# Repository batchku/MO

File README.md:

# MO
Mobile Objects for Music (MOM), Mobile Object for Drawing (MOD), and ...

## Installation

First: clone this repo:
```
git clone git@github.com:batchku/MO.git
```

Then: This repo relies on a [aLib-pd](https://github.com/batchku/aLib-pd) as a submodule. You can either clone that repo separately, or use this command within the MO repository to pull the submodule:

```
git submodule update --init --recursive
```
### nameChange.sh

To test for resulting name change use "test":

```./nameChanger.sh test searchTerm wordToReplaceWith```

To actually change use "change":

```./nameChanger.sh change searchTerm wordToReplaceWith```

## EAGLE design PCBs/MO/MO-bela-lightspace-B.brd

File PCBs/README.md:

# PCBs
###   GERBERS
Gerber files for PCB orders
###   MO
Board + Schem files for MO, this is the primary PCB collection
###   MOM
Board + Schem files specifically for MOM
###   Processor
Header, .txt, and XML file generator code

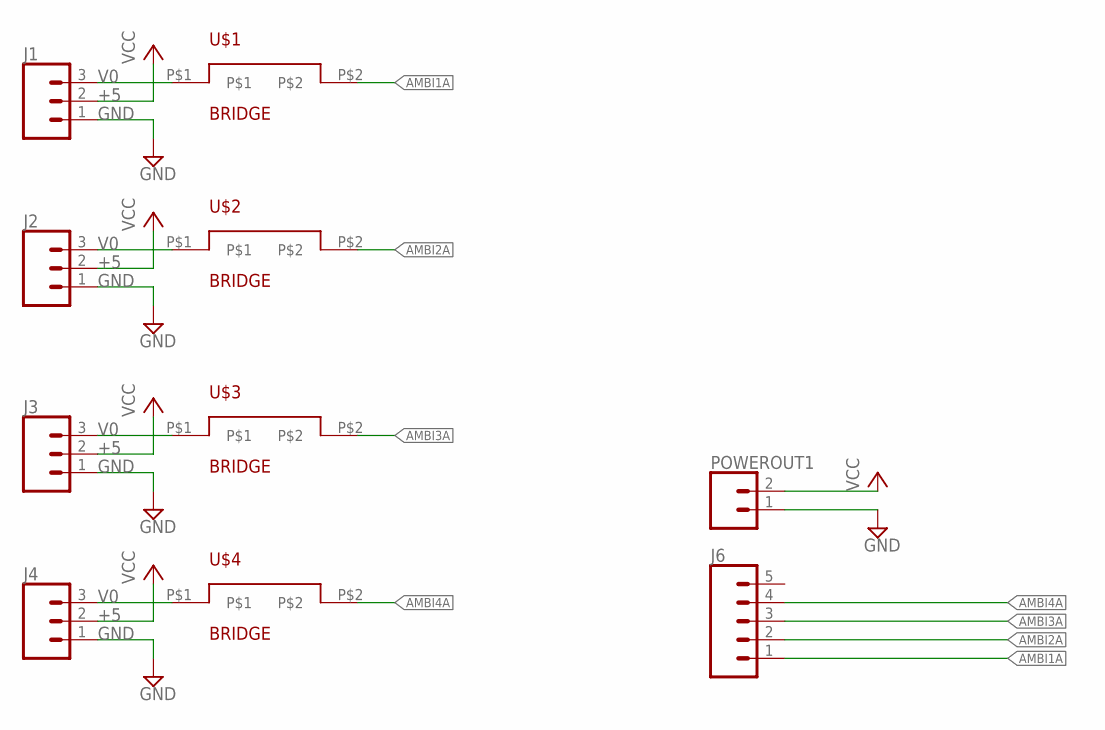
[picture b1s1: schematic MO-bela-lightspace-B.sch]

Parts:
J1, J2, J3, J4: CONN_03LOCK; 1X03_LOCK
J6: CONN_05LOCK; 1X05_LOCK
POWEROUT1: CONN_02LOCK; 1X02_LOCK
U$1, U$2, U$3, U$4: BRIDGE

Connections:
AMBI1A: J6.1, U$1.P$2
AMBI2A: J6.2, U$2.P$2
AMBI3A: J6.3, U$3.P$2
AMBI4A: J6.4, U$4.P$2
GND: J1.1, J2.1, J3.1, POWEROUT1.1
MNOVE: J4.1
unnamed: J1.3, U$1.P$1
unnamed: J2.3, U$2.P$1
unnamed: J3.3, U$3.P$1
unnamed: J4.3, U$4.P$1
VCC: J1.2, J2.2, J3.2, J4.2, POWEROUT1.2

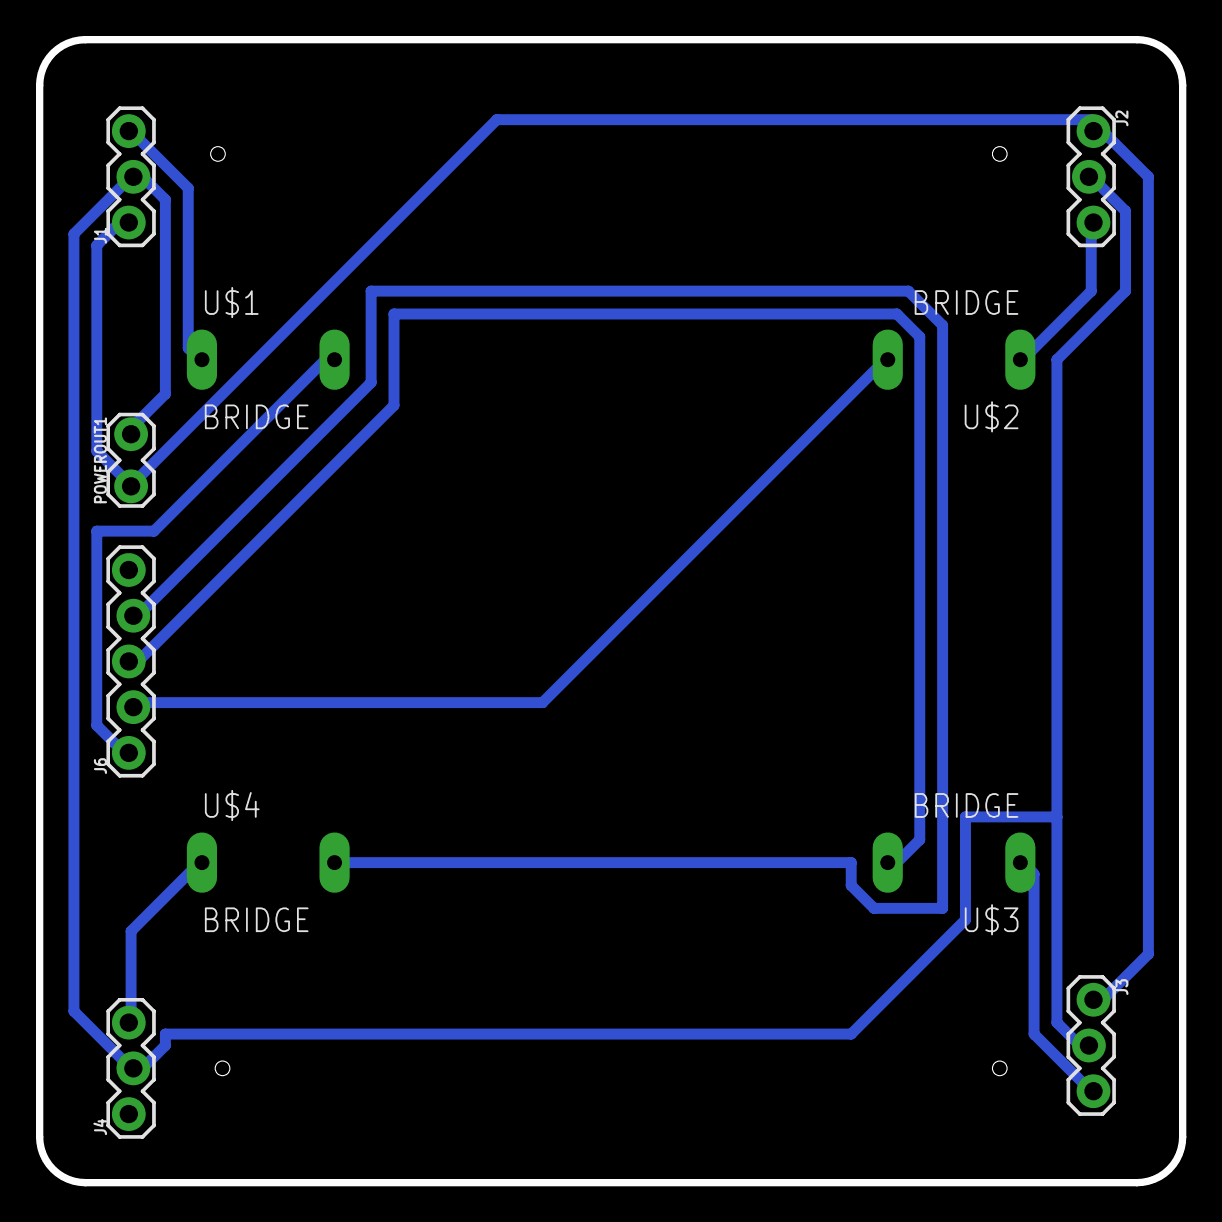
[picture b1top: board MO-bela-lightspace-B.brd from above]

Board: 2 copper layers, 63.5 x 63.5 mm, 10 parts (0 on the bottom side), 10 nets.

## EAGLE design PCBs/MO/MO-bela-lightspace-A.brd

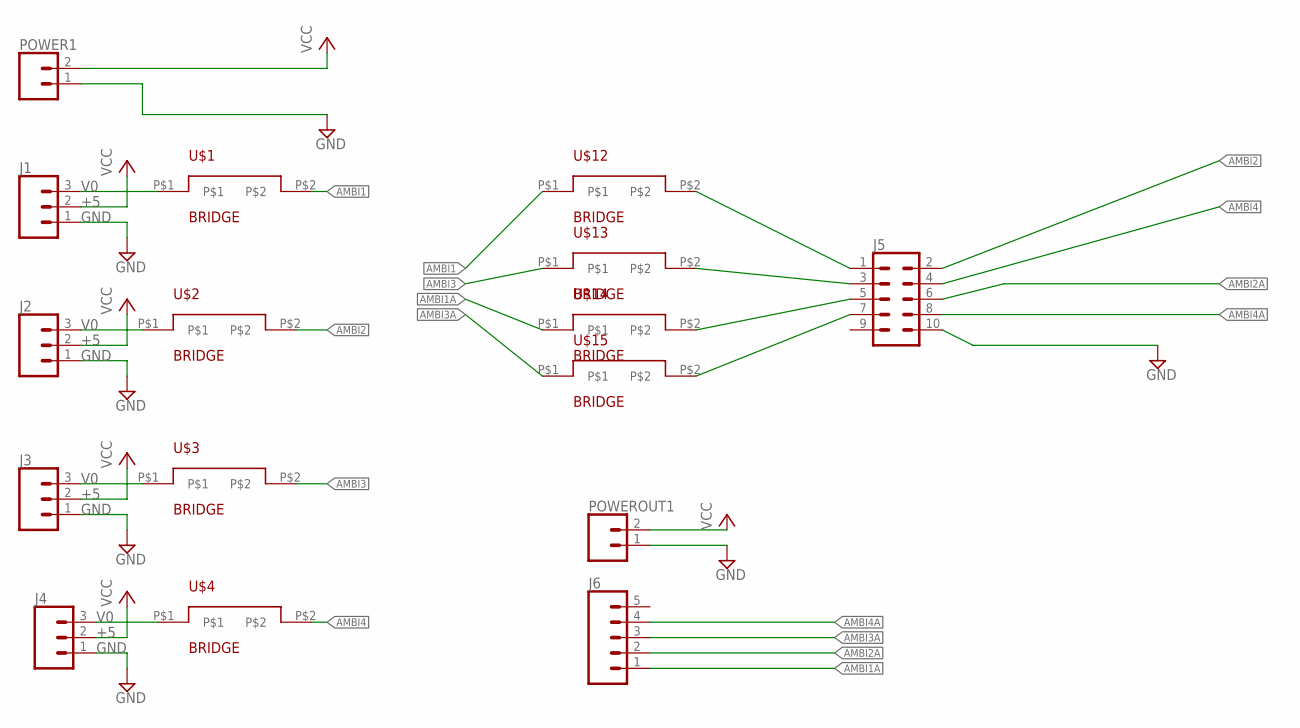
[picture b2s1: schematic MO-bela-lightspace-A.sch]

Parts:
J1, J2, J3, J4: CONN_03LOCK; 1X03_LOCK
J5: CONN_05X2SHD_LOCK; 2X5-SHROUDED_LOCK
J6: CONN_05LOCK; 1X05_LOCK
POWER1: CONN_02LOCK; 1X02_LOCK
POWEROUT1: CONN_02LOCK; 1X02_LOCK
U$1, U$2, U$3, U$4, U$12, U$13, U$14, U$15: BRIDGE

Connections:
AMBI1: U$1.P$2, U$12.P$1
AMBI1A: J6.1, U$14.P$1
AMBI2: J5.2, U$2.P$2
AMBI2A: J5.6, J6.2
AMBI3: U$3.P$2, U$13.P$1
AMBI3A: J6.3, U$15.P$1
AMBI4: J5.4, U$4.P$2
AMBI4A: J5.8, J6.4
GND: J1.1, J2.1, J3.1, J4.1, J5.10, POWER1.1, POWEROUT1.1
unnamed: J1.3, U$1.P$1
unnamed: J2.3, U$2.P$1
unnamed: J3.3, U$3.P$1
unnamed: J4.3, U$4.P$1
unnamed: J5.1, U$12.P$2
unnamed: J5.3, U$13.P$2
unnamed: J5.5, U$14.P$2
unnamed: J5.7, U$15.P$2
VCC: J1.2, J2.2, J3.2, J4.2, POWER1.2, POWEROUT1.2

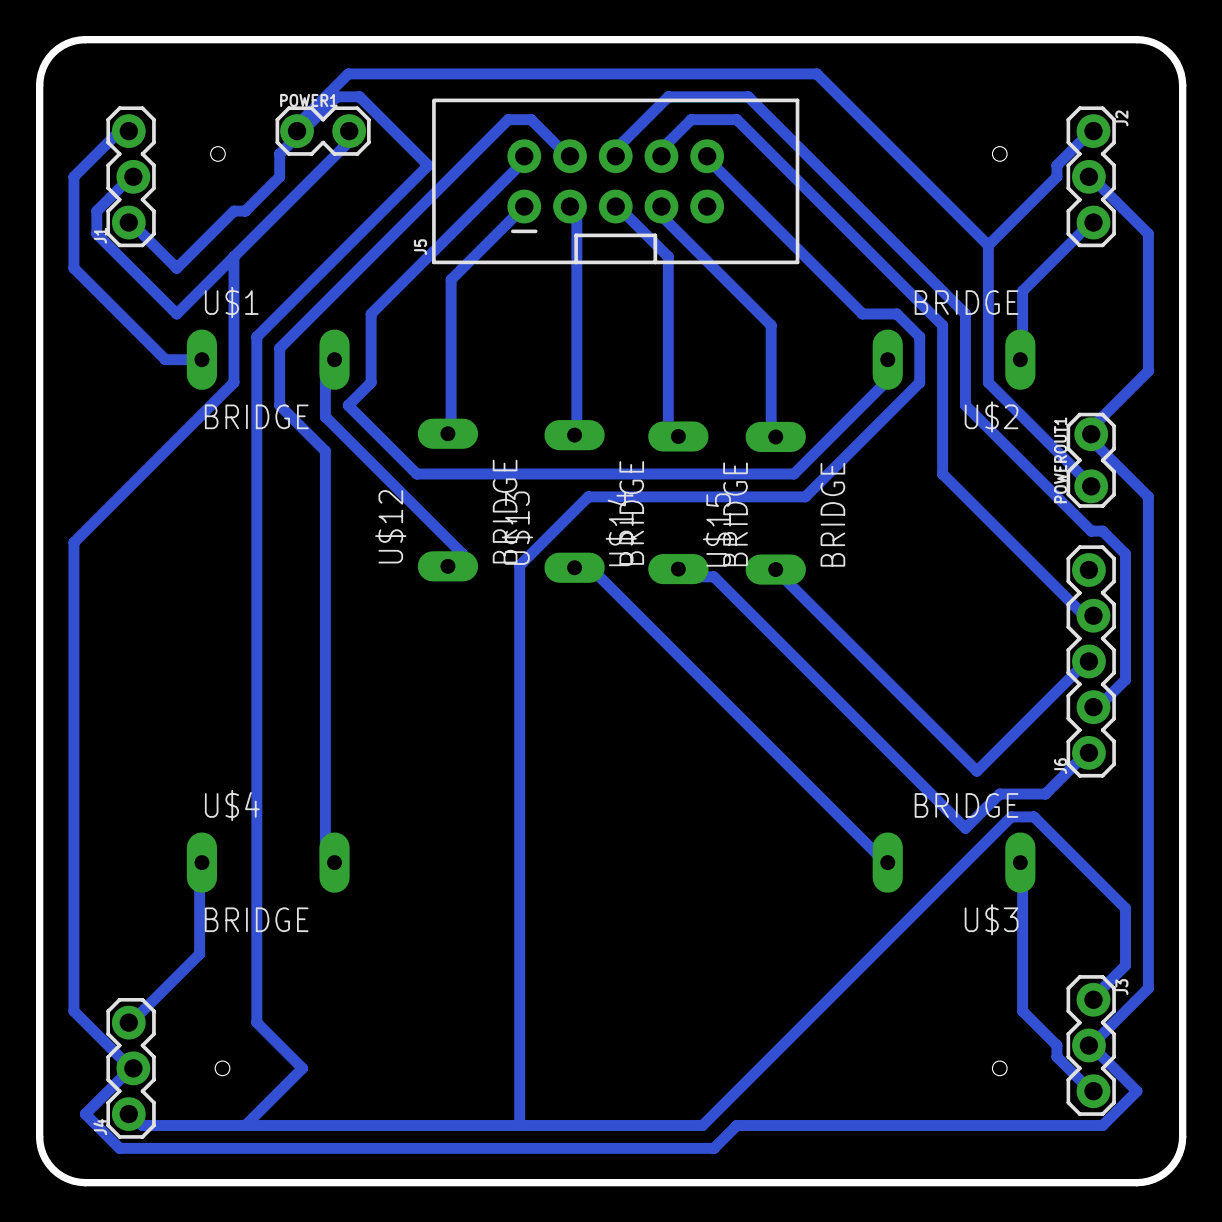
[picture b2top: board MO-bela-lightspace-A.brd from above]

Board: 2 copper layers, 63.5 x 63.5 mm, 16 parts (0 on the bottom side), 18 nets.

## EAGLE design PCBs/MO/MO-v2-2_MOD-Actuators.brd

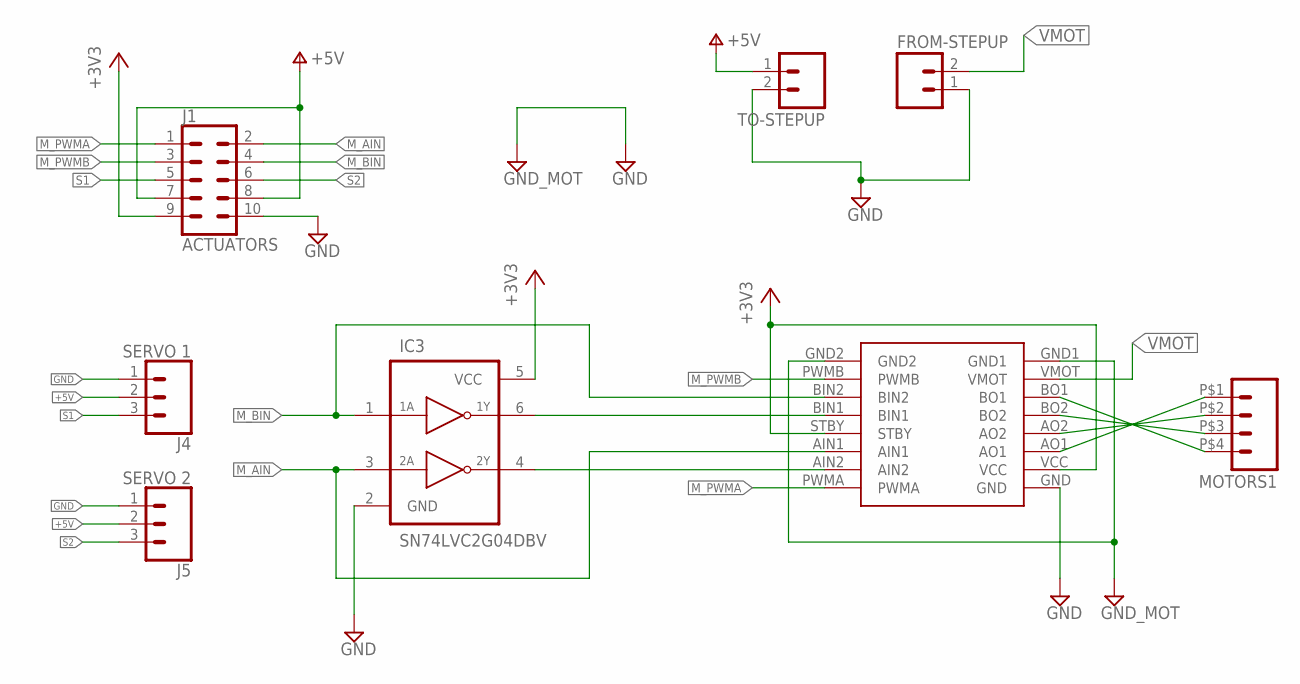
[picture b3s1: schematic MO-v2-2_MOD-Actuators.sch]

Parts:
FROM-STEPUP: M02LOCK; 1X02_LOCK
IC3: SN74LVC2G04DBV; SOT23-6
J1: ACTUATORS; 2X5-SHROUDED_LOCK
J4: SERVO 1; 1X03_LOCK@1
J5: SERVO 2; 1X03_LOCK@1
MOTORS1: M04; SPRINGTERMINAL-2.54MM-4
TO-STEPUP: M02LOCK; 1X02_LOCK
U$7: POLOLU_TB6612FNG

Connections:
+3V3: IC3.5 (VCC), J1.9, U$7.STBY, U$7.VCC
+5V: J1.7, J1.8, J4.2, J5.2, TO-STEPUP.1
GND: FROM-STEPUP.1, IC3.2 (GND), J1.10, J4.1, J5.1, TO-STEPUP.2, U$7.GND
GND_MOT: U$7.GND1, U$7.GND2
M_AIN: IC3.3 (2A), J1.2, U$7.AIN1
M_BIN: IC3.1 (1A), J1.4, U$7.BIN2
M_PWMA: J1.1, U$7.PWMA
M_PWMB: J1.3, U$7.PWMB
unnamed: MOTORS1.P$1 (1), U$7.AO1
unnamed: MOTORS1.P$2 (2), U$7.AO2
unnamed: MOTORS1.P$3 (3), U$7.BO2
unnamed: MOTORS1.P$4 (4), U$7.BO1
unnamed: IC3.6 (1Y), U$7.BIN1
unnamed: IC3.4 (2Y), U$7.AIN2
S1: J1.5, J4.3
S2: J1.6, J5.3
VMOT: FROM-STEPUP.2, U$7.VMOT

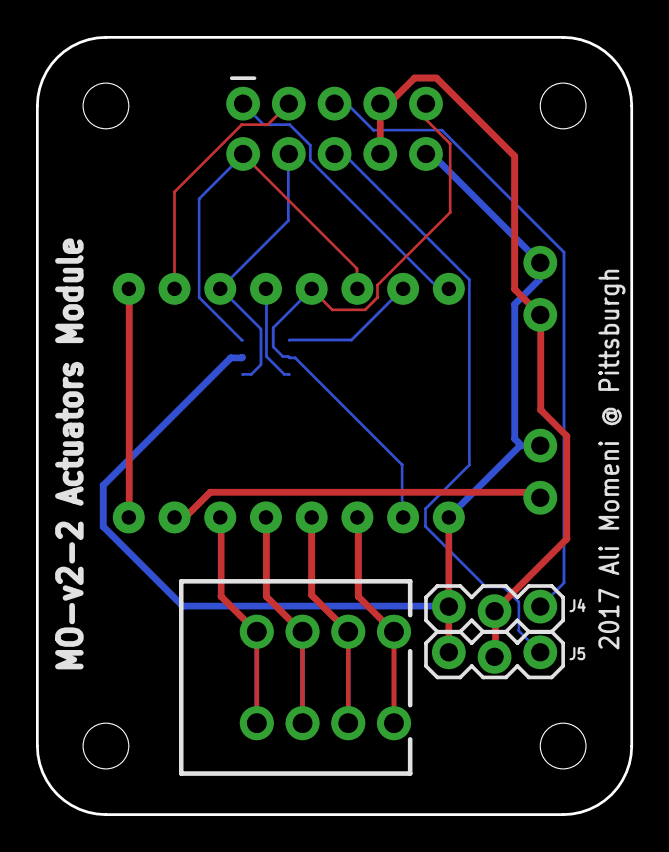
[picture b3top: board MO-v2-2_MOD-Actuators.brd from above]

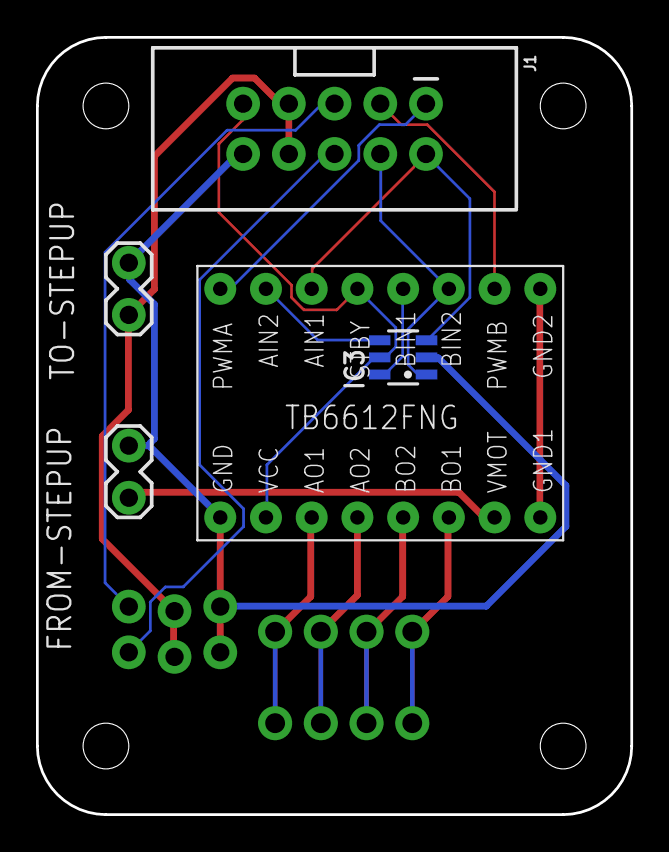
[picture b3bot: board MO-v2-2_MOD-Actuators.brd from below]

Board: 2 copper layers, 33.0 x 43.2 mm, 8 parts (5 on the bottom side), 17 nets.

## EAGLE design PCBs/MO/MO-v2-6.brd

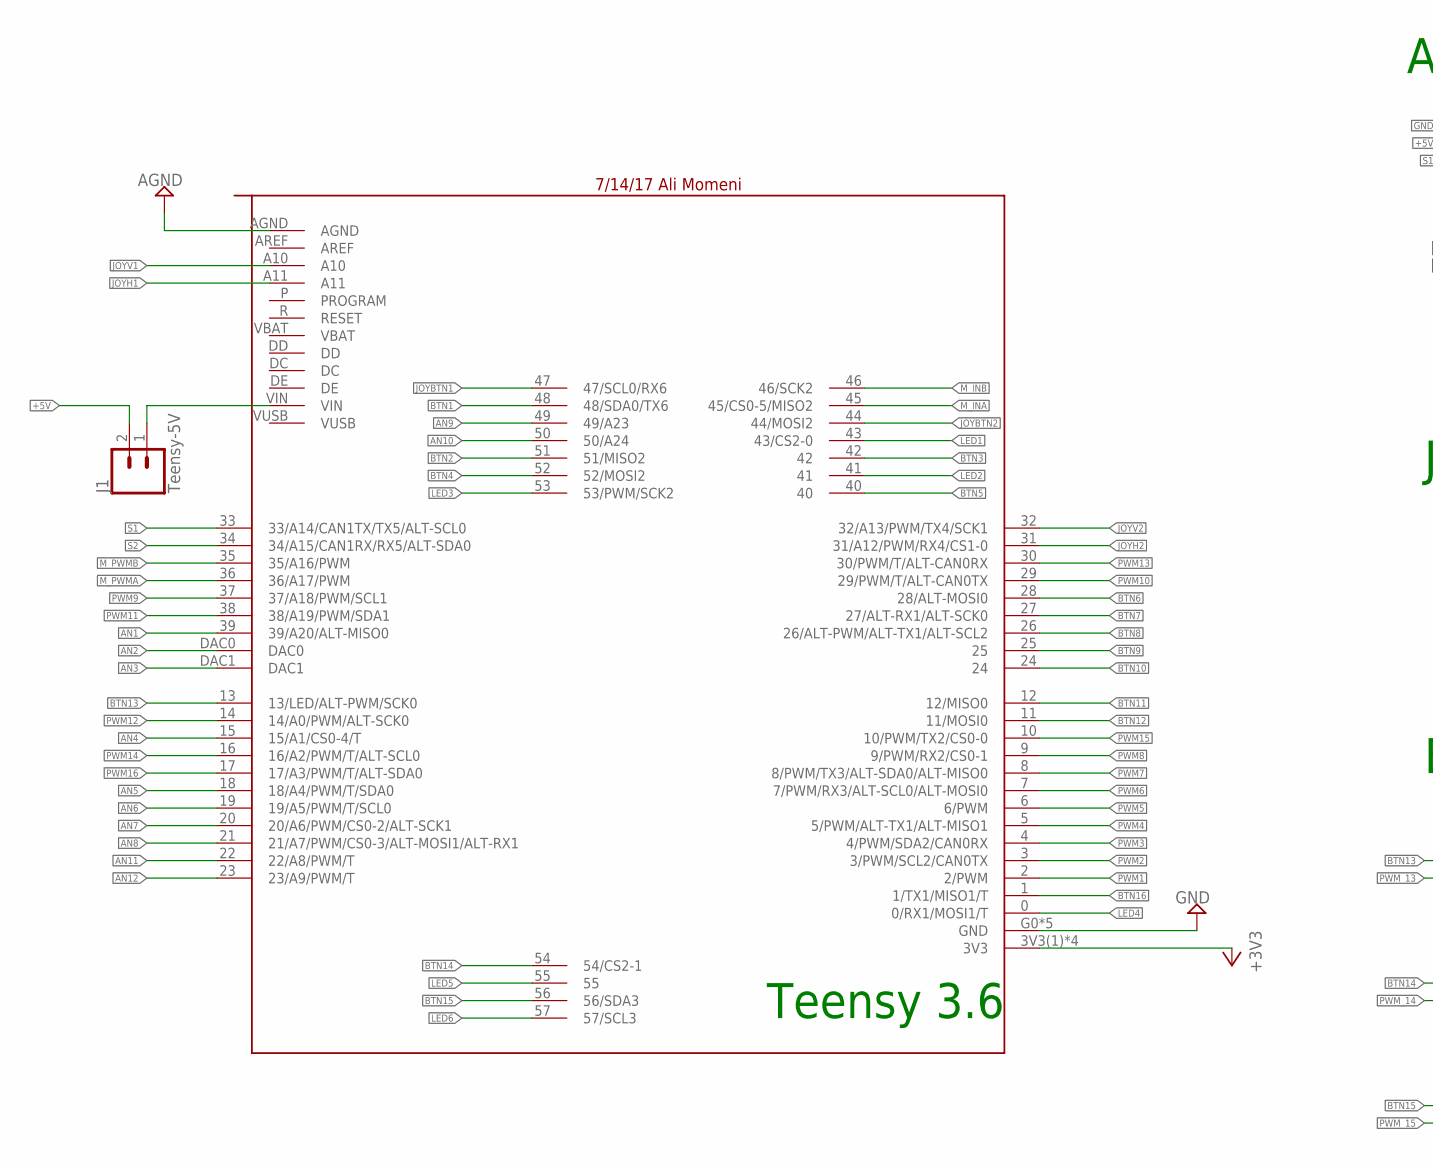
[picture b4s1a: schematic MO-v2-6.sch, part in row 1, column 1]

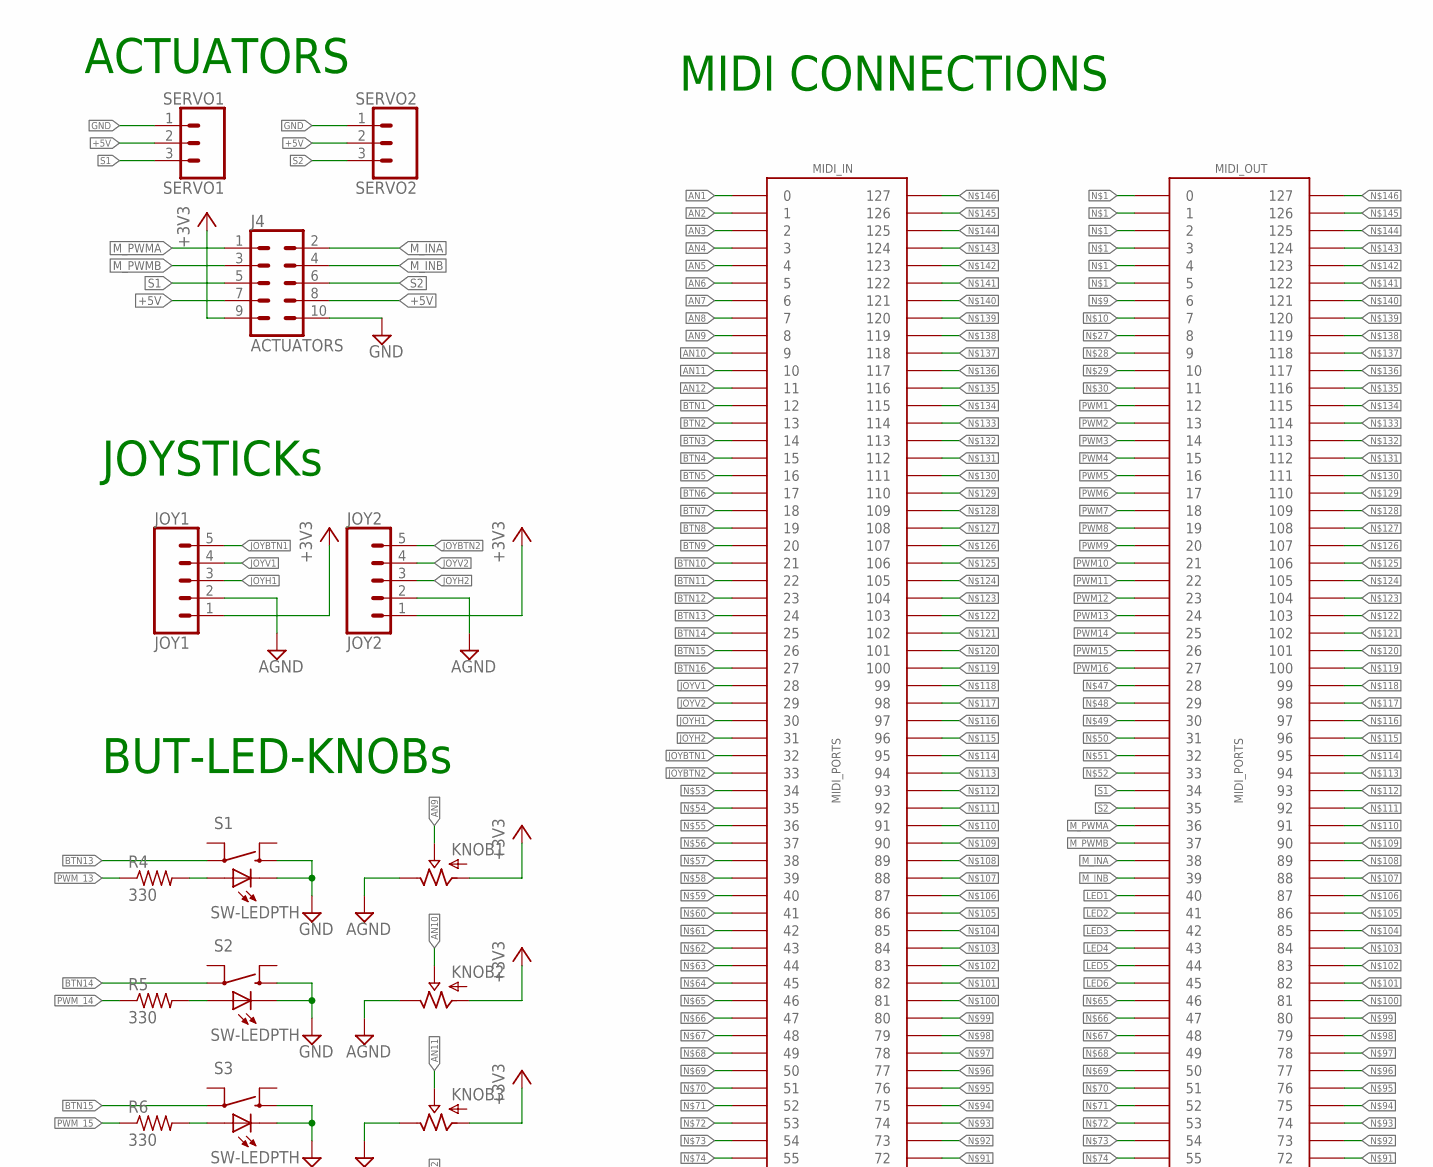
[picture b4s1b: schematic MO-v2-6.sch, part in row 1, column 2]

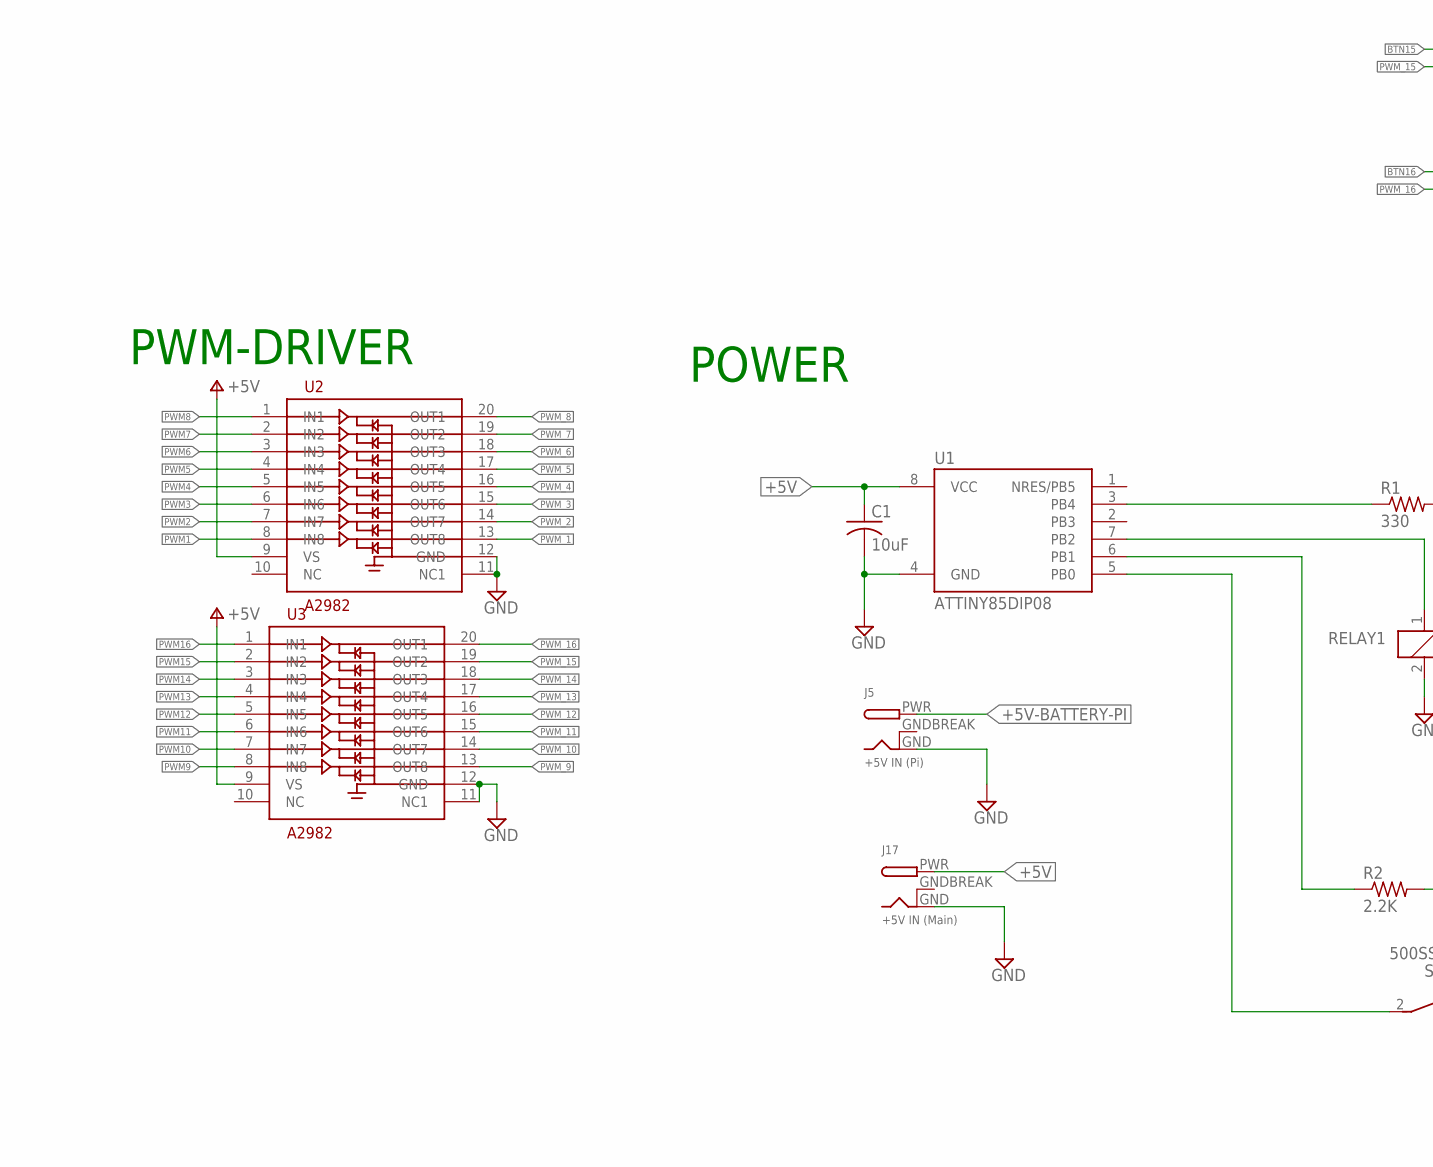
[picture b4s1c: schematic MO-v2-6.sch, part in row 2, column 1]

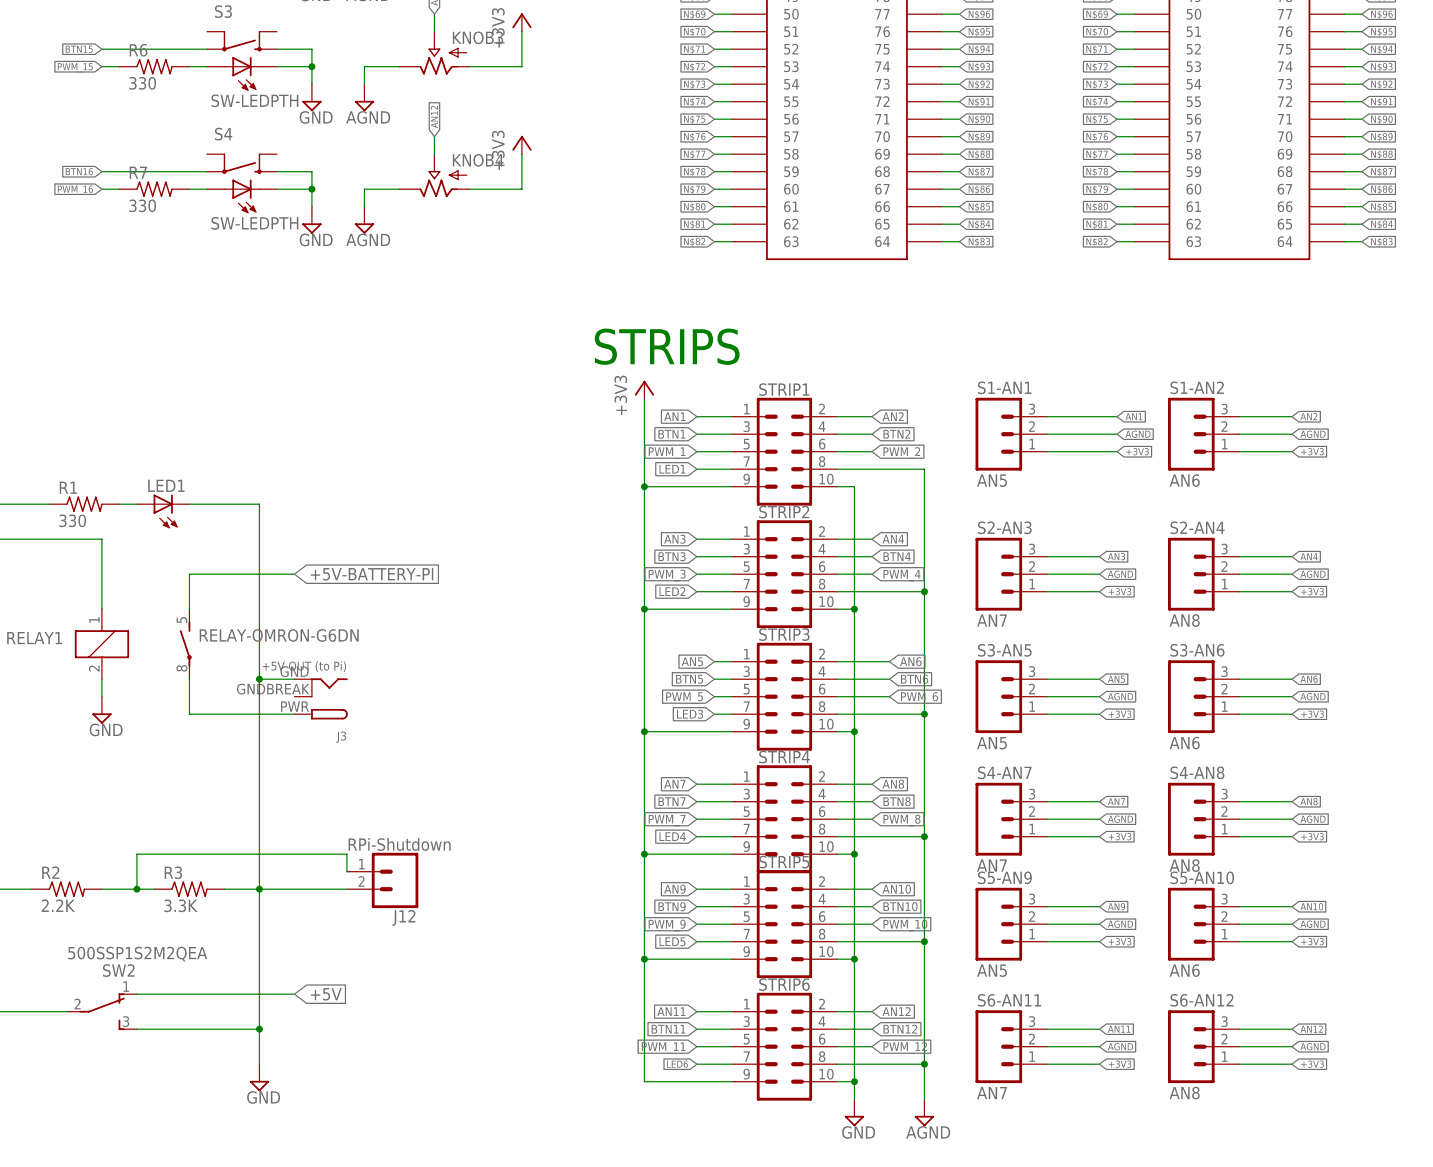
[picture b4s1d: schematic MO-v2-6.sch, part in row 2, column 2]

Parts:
C1: 10uF; C050-024X044
J1: Teensy-5V; 1X02_LOCK
J3: +5V OUT (to Pi); DCJACK_2MM_PTH
J4: ACTUATORS; 2X5-SHROUDED_LOCK
J5: +5V IN (Pi); DCJACK_2MM_PTH
J12: RPi-Shutdown; 1X02_LOCK
J17: +5V IN (Main); DCJACK_2MM_PTH
JOY1: JOY1; 1X05_LOCK
JOY2: JOY2; 1X05_LOCK
KNOB1, KNOB2, KNOB3, KNOB4: POTALPHA_RD901; POT_ALPHA_RD901F-40-(L)R1
LED1: LED3MM
R1, R4, R5, R6, R7: 330; 0204/7
R2: 2.2K; 0204/7
R3: 3.3K; 0204/7
RELAY1: RELAY-OMRON-G6DN; G6DN-1A
S1, S2, S3, S4: SW-LEDPTH; SWITCH_TR2-MOMENTARY-LED
S1-AN1, S3-AN5, S5-AN9: AN5; 1X03_LOCK
S1-AN2, S3-AN6, S5-AN10: AN6; 1X03_LOCK
S2-AN3, S4-AN7, S6-AN11: AN7; 1X03_LOCK
S2-AN4, S4-AN8, S6-AN12: AN8; 1X03_LOCK
SERVO1: SERVO1; 1X03_LOCK@1
SERVO2: SERVO2; 1X03_LOCK@1
STRIP1, STRIP2, STRIP3, STRIP4, STRIP5, STRIP6: CONN_05X2SHD_LOCK; 2X5-SHROUDED_LOCK
SW2: 500SSP1S2M2QEA; SWITCH_SPDT_500SSP1S2M2QEA
TEENSY: TEENSY3_6-ALI_NO-USB-HOST; TEENSY3-6_NO-USB-HOST
U1: ATTINY85DIP08; DIP08
U2, U3: A2982; SOIC20

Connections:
+3V3: J4.9, JOY1.1, JOY2.1, KNOB1.1 (IN), KNOB2.1 (IN), KNOB3.1 (IN), KNOB4.1 (IN), S1-AN1.1, S1-AN2.1, S2-AN3.1, S2-AN4.1, S3-AN5.1, S3-AN6.1, S4-AN7.1, S4-AN8.1, S5-AN9.1, S5-AN10.1, S6-AN11.1, S6-AN12.1, STRIP1.9, STRIP2.9, STRIP3.9, STRIP4.9, STRIP5.9, STRIP6.9, TEENSY.3V3(1) (3V3), TEENSY.3V3(2) (3V3), TEENSY.3V3(3) (3V3), TEENSY.3V3(4) (3V3)
+5V: C1.1, J1.2, J4.7, J4.8, J17.PWR, SERVO1.2, SERVO2.2, SW2.1, U1.8 (VCC), U2.9 (VS), U3.9 (VS)
+5V-BATTERY-PI: J5.PWR, RELAY1.5
AGND: JOY1.2, JOY2.2, KNOB1.3 (OUT), KNOB2.3 (OUT), KNOB3.3 (OUT), KNOB4.3 (OUT), S1-AN1.2, S1-AN2.2, S2-AN3.2, S2-AN4.2, S3-AN5.2, S3-AN6.2, S4-AN7.2, S4-AN8.2, S5-AN9.2, S5-AN10.2, S6-AN11.2, S6-AN12.2, STRIP1.8, STRIP2.8, STRIP3.8, STRIP4.8, STRIP5.8, STRIP6.8, TEENSY.AGND
AN1: S1-AN1.3, STRIP1.1, TEENSY.39 (39/A20/ALT-MISO0)
AN2: S1-AN2.3, STRIP1.2, TEENSY.DAC0
AN3: S2-AN3.3, STRIP2.1, TEENSY.DAC1
AN4: S2-AN4.3, STRIP2.2, TEENSY.15 (15/A1/CS0-4/T)
AN5: S3-AN5.3, STRIP3.1, TEENSY.18 (18/A4/PWM/T/SDA0)
AN6: S3-AN6.3, STRIP3.2, TEENSY.19 (19/A5/PWM/T/SCL0)
AN7: S4-AN7.3, STRIP4.1, TEENSY.20 (20/A6/PWM/CS0-2/ALT-SCK1)
AN8: S4-AN8.3, STRIP4.2, TEENSY.21 (21/A7/PWM/CS0-3/ALT-MOSI1/ALT-RX1)
AN9: KNOB1.2 (WIPER), S5-AN9.3, STRIP5.1, TEENSY.49 (49/A23)
AN10: KNOB2.2 (WIPER), S5-AN10.3, STRIP5.2, TEENSY.50 (50/A24)
AN11: KNOB3.2 (WIPER), S6-AN11.3, STRIP6.1, TEENSY.22 (22/A8/PWM/T)
AN12: KNOB4.2 (WIPER), S6-AN12.3, STRIP6.2, TEENSY.23 (23/A9/PWM/T)
BTN1: STRIP1.3, TEENSY.48 (48/SDA0/TX6)
BTN2: STRIP1.4, TEENSY.51 (51/MISO2)
BTN3: STRIP2.3, TEENSY.42
BTN4: STRIP2.4, TEENSY.52 (52/MOSI2)
BTN5: STRIP3.3, TEENSY.40
BTN6: STRIP3.4, TEENSY.28 (28/ALT-MOSI0)
BTN7: STRIP4.3, TEENSY.27 (27/ALT-RX1/ALT-SCK0)
BTN8: STRIP4.4, TEENSY.26 (26/ALT-PWM/ALT-TX1/ALT-SCL2)
BTN9: STRIP5.3, TEENSY.25
BTN10: STRIP5.4, TEENSY.24
BTN11: STRIP6.3, TEENSY.12 (12/MISO0)
BTN12: STRIP6.4, TEENSY.11 (11/MOSI0)
BTN13: S1.3, TEENSY.13 (13/LED/ALT-PWM/SCK0)
BTN14: S2.3, TEENSY.54 (54/CS2-1)
BTN15: S3.3, TEENSY.56 (56/SDA3)
BTN16: S4.3, TEENSY.1 (1/TX1/MISO1/T)
GND: C1.2, J3.GND, J4.10, J5.GND, J12.2, J17.GND, LED1.K (C), R3.2, RELAY1.2, S1.1, S1.C, S2.1, S2.C, S3.1, S3.C, S4.1, S4.C, SERVO1.1, SERVO2.1, STRIP1.10, STRIP2.10, STRIP3.10, STRIP4.10, STRIP5.10, STRIP6.10, SW2.3, TEENSY.G0 (GND), TEENSY.G1 (GND), TEENSY.G2 (GND), TEENSY.G3 (GND), TEENSY.G6 (GND), U1.4 (GND), U2.11 (NC1), U2.12 (GND), U3.11 (NC1), U3.12 (GND)
GNDBREAK: J3.GNDBREAK, J5.GNDBREAK, J17.GNDBREAK
JOYBTN1: JOY1.5, TEENSY.47 (47/SCL0/RX6)
JOYBTN2: JOY2.5, TEENSY.44 (44/MOSI2)
JOYH1: JOY1.3, TEENSY.A11
JOYH2: JOY2.3, TEENSY.31 (31/A12/PWM/RX4/CS1-0)
JOYV1: JOY1.4, TEENSY.A10
JOYV2: JOY2.4, TEENSY.32 (32/A13/PWM/TX4/SCK1)
LED1: STRIP1.7, TEENSY.43 (43/CS2-0)
LED2: STRIP2.7, TEENSY.41
LED3: STRIP3.7, TEENSY.53 (53/PWM/SCK2)
LED4: STRIP4.7, TEENSY.0 (0/RX1/MOSI1/T)
LED5: STRIP5.7, TEENSY.55
LED6: STRIP6.7, TEENSY.57 (57/SCL3)
M_INA: J4.2, TEENSY.45 (45/CS0-5/MISO2)
M_INB: J4.4, TEENSY.46 (46/SCK2)
M_PWMA: J4.1, TEENSY.36 (36/A17/PWM)
M_PWMB: J4.3, TEENSY.35 (35/A16/PWM)
unnamed: LED1.A, R1.2
unnamed: R4.2, S1.A
unnamed: R5.2, S2.A
unnamed: J12.1, R2.2, R3.1
unnamed: R6.2, S3.A
unnamed: J1.1, TEENSY.VIN
unnamed: R7.2, S4.A
PI-REST: R2.1, U1.6 (PB1)
PWM1: TEENSY.2 (2/PWM), U2.8 (IN8)
PWM2: TEENSY.3 (3/PWM/SCL2/CAN0TX), U2.7 (IN7)
PWM3: TEENSY.4 (4/PWM/SDA2/CAN0RX), U2.6 (IN6)
PWM4: TEENSY.5 (5/PWM/ALT-TX1/ALT-MISO1), U2.5 (IN5)
PWM5: TEENSY.6 (6/PWM), U2.4 (IN4)
PWM6: TEENSY.7 (7/PWM/RX3/ALT-SCL0/ALT-MOSI0), U2.3 (IN3)
PWM7: TEENSY.8 (8/PWM/TX3/ALT-SDA0/ALT-MISO0), U2.2 (IN2)
PWM8: TEENSY.9 (9/PWM/RX2/CS0-1), U2.1 (IN1)
PWM9: TEENSY.37 (37/A18/PWM/SCL1), U3.8 (IN8)
PWM10: TEENSY.29 (29/PWM/T/ALT-CAN0TX), U3.7 (IN7)
PWM11: TEENSY.38 (38/A19/PWM/SDA1), U3.6 (IN6)
PWM12: TEENSY.14 (14/A0/PWM/ALT-SCK0), U3.5 (IN5)
PWM13: TEENSY.30 (30/PWM/T/ALT-CAN0RX), U3.4 (IN4)
PWM14: TEENSY.16 (16/A2/PWM/T/ALT-SCL0), U3.3 (IN3)
PWM15: TEENSY.10 (10/PWM/TX2/CS0-0), U3.2 (IN2)
PWM16: TEENSY.17 (17/A3/PWM/T/ALT-SDA0), U3.1 (IN1)
PWM_1: STRIP1.5, U2.13 (OUT8)
PWM_2: STRIP1.6, U2.14 (OUT7)
PWM_3: STRIP2.5, U2.15 (OUT6)
PWM_4: STRIP2.6, U2.16 (OUT5)
PWM_5: STRIP3.5, U2.17 (OUT4)
PWM_6: STRIP3.6, U2.18 (OUT3)
PWM_7: STRIP4.5, U2.19 (OUT2)
PWM_8: STRIP4.6, U2.20 (OUT1)
PWM_9: STRIP5.5, U3.13 (OUT8)
PWM_10: STRIP5.6, U3.14 (OUT7)
PWM_11: STRIP6.5, U3.15 (OUT6)
PWM_12: STRIP6.6, U3.16 (OUT5)
PWM_13: R4.1, U3.17 (OUT4)
PWM_14: R5.1, U3.18 (OUT3)
PWM_15: R6.1, U3.19 (OUT2)
PWM_16: R7.1, U3.20 (OUT1)
RELAY-PWR: J3.PWR, RELAY1.8
S1: J4.5, SERVO1.3, TEENSY.33 (33/A14/CAN1TX/TX5/ALT-SCL0)
S2: J4.6, SERVO2.3, TEENSY.34 (34/A15/CAN1RX/RX5/ALT-SDA0)
TINY_LED: R1.1, U1.3 (PB4)
TINY_RELAY: RELAY1.1, U1.7 (PB2)
TINY_SWITCH: SW2.2, U1.5 (PB0)

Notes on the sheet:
BUT-LED-KNOBs
JOYSTICKs
PWM-DRIVER
STRIPS
ACTUATORS
POWER
Teensy 3.6
MIDI CONNECTIONS

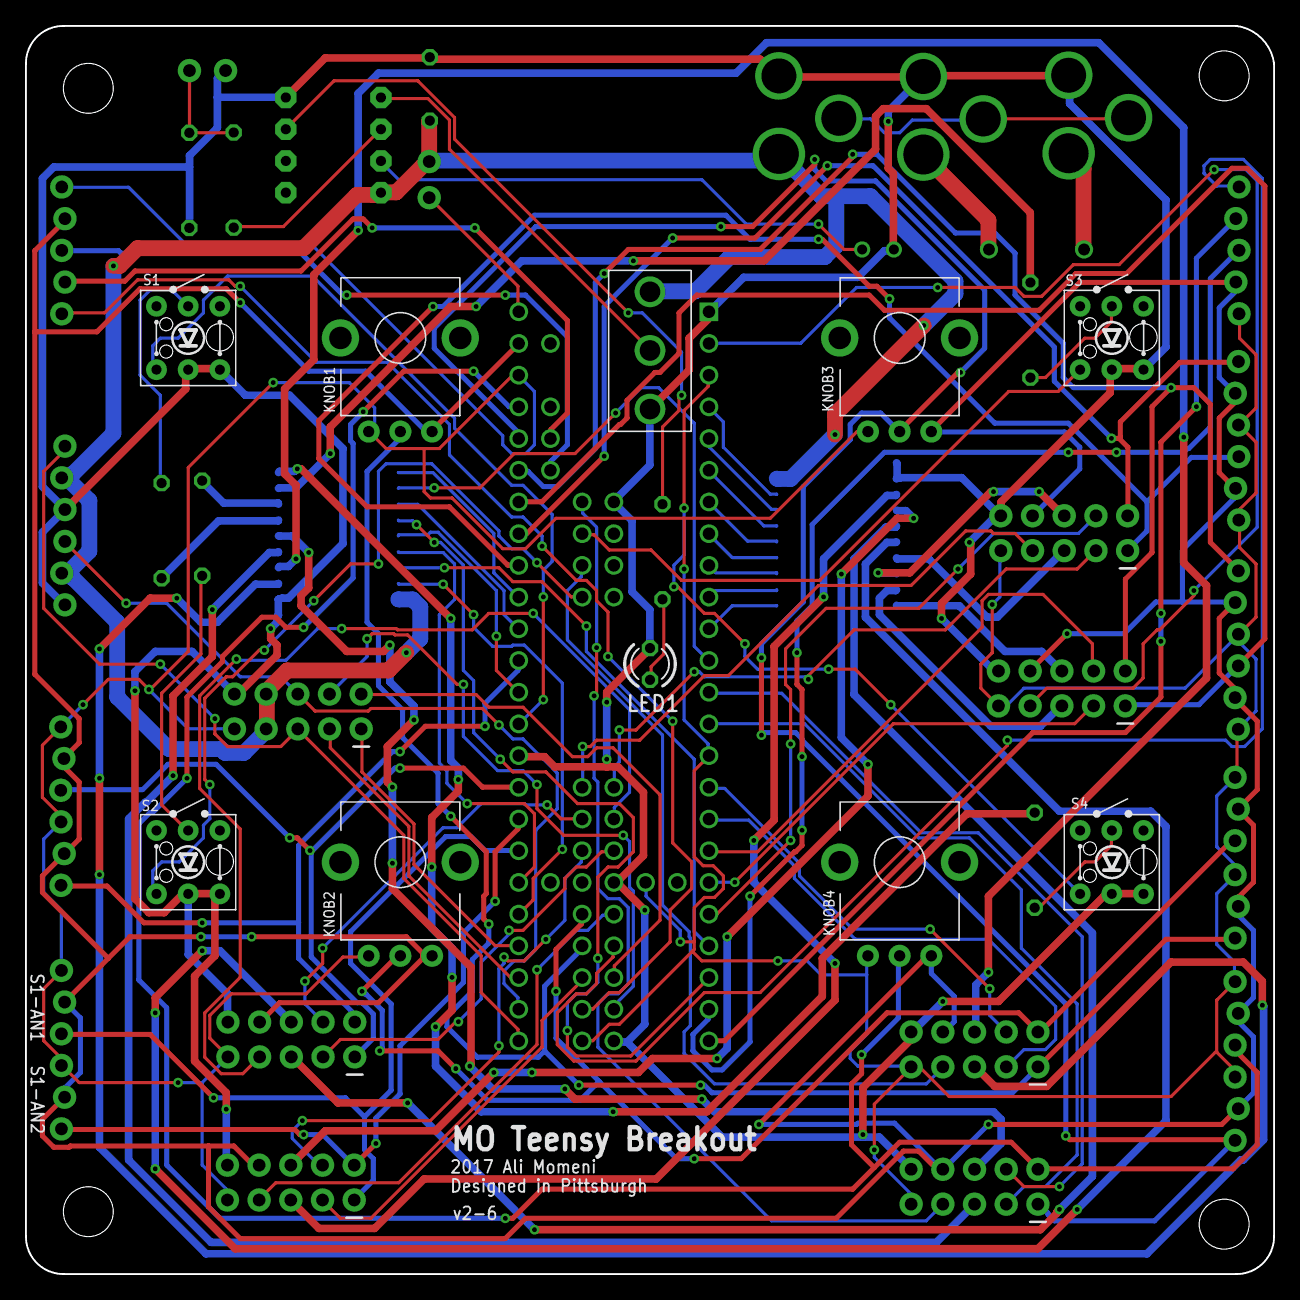
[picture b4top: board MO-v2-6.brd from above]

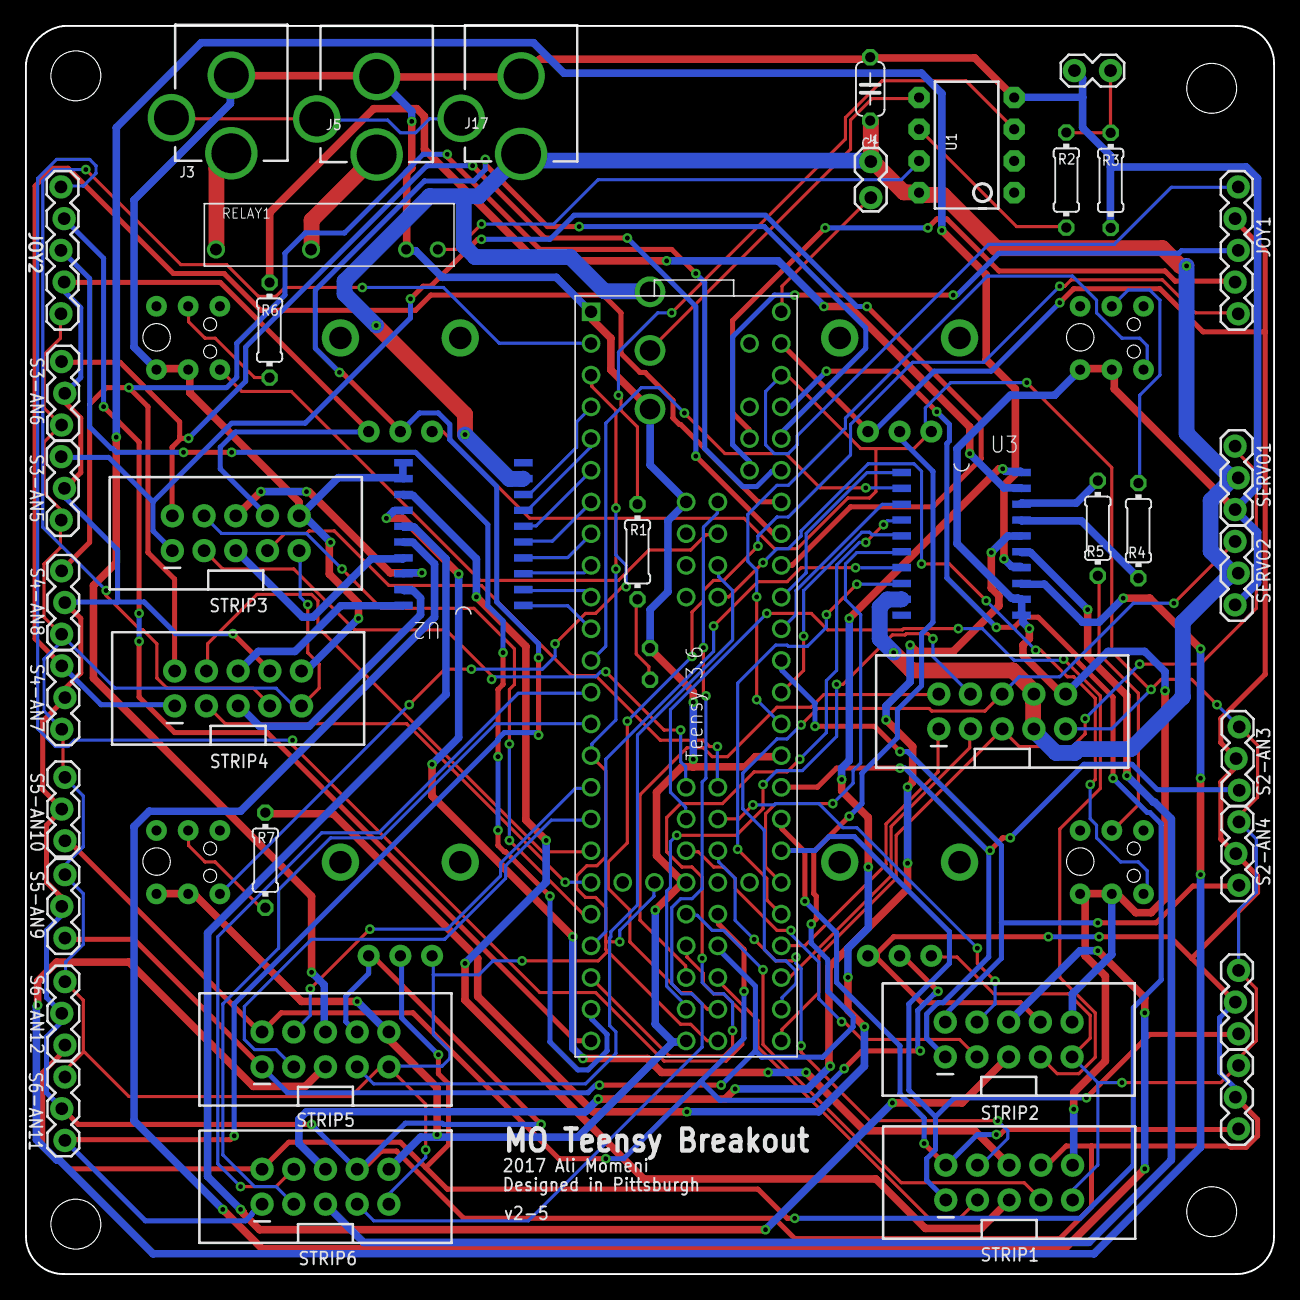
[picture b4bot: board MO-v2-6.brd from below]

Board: 2 copper layers, 100.0 x 100.0 mm, 51 parts (41 on the bottom side), 96 nets.

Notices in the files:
parts and their libraries:
SparkFun-Connectors: Licensing: Creative Commons ShareAlike 4.0 International - https://creativecommons.org/licenses/by-sa/4.0
74LV: Copyright (C) 2008, Bob Starr
